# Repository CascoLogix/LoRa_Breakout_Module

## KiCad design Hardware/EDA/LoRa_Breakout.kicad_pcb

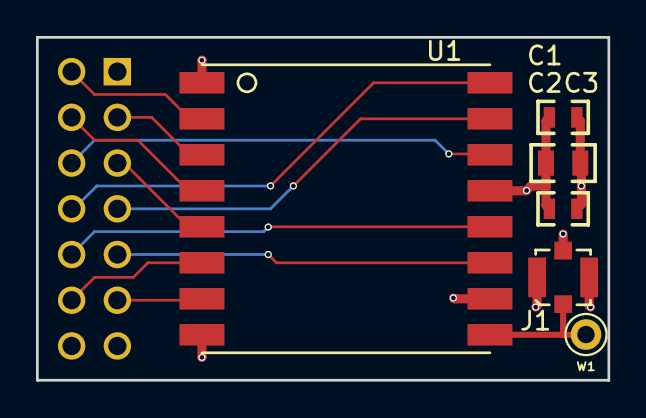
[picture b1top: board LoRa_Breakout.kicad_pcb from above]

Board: 4 copper layers, 31.8 x 19.0 mm, 7 parts (1 on the bottom side), 14 nets.

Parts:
C1: 10u; C0805
C2: 1u; C0603
C3: 0.1u; C0603
J1: u.FL; U.FL-R-SMT
P1: HEADER_2x7; HEADER_100MIL_2R14P_PTH
U1: RFM95W
W1: WIRE_PAD_26AWG; WIRE_PAD_22AWG

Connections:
+3V3: C1.1, C2.1, C3.1, P1.13, U1.13
CS: P1.5, U1.5
DIO0: P1.6, U1.14
DIO1: P1.7, U1.15
DIO2: P1.8, U1.16
DIO3: P1.9, U1.11
DIO4: P1.10, U1.12
DIO5: P1.11, U1.7
GND: C1.2, C2.2, C3.2, J1.2, J1.3, J1.4, P1.1, P1.14, U1.1, U1.8, U1.10
MISO: P1.2, U1.2
MOSI: P1.3, U1.3
unnamed: J1.1, U1.9, W1.1
RESET: P1.12, U1.6
SCK: P1.4, U1.4
